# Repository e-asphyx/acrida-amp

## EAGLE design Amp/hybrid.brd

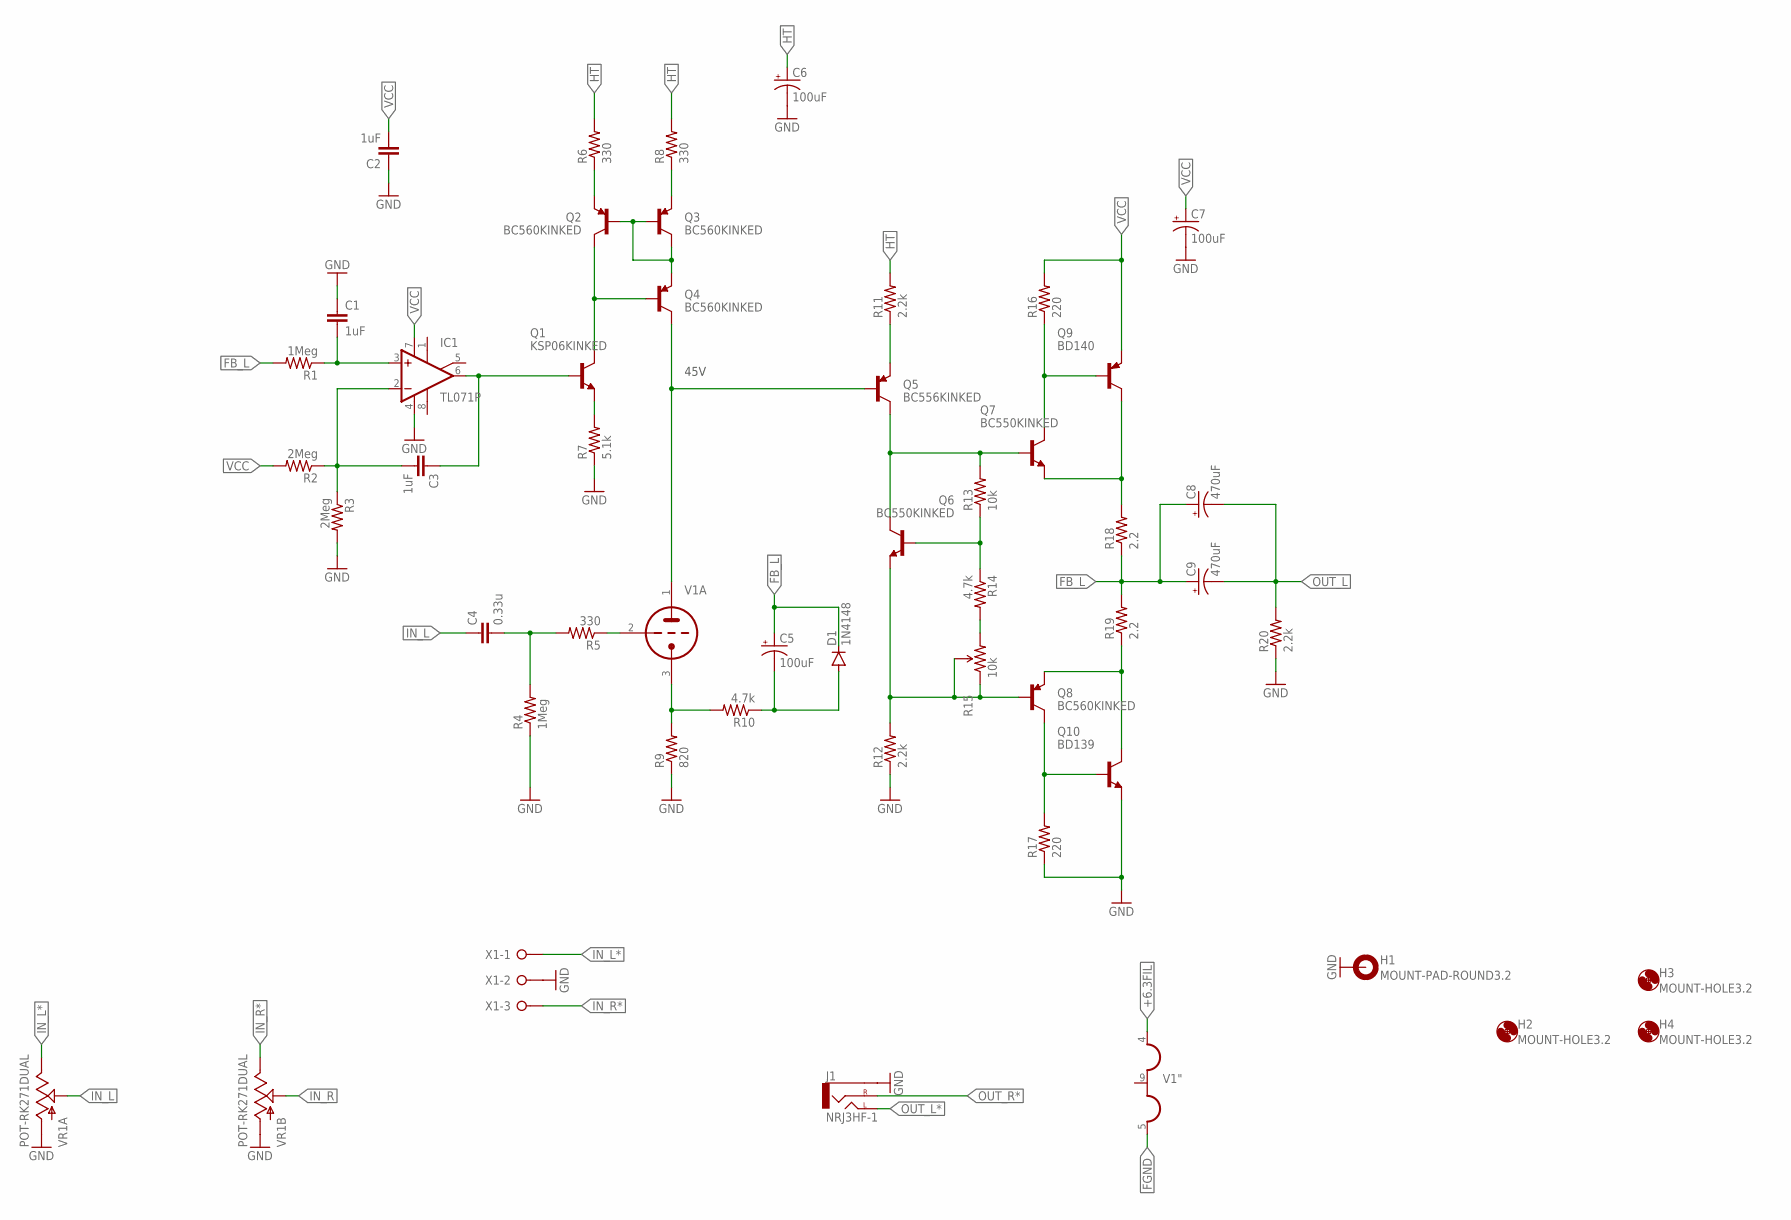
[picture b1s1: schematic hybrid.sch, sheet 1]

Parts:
C1, C3: 1uF; C5B5
C2: 1uF; CAP-PTH-SMALL
C4: 0.33u; C5B7.2
C5: 100uF; CPOL-RADIAL-8/3.5
C6, C7: 100uF; CPOL-RADIAL-12.5/5
C8, C9: 470uF; CPOL-RADIAL-12.5/5
D1: 1N4148; DIODE-1N4148
H1: MOUNT-PAD-ROUND3.2; 3,2-PAD
H2, H3, H4: MOUNT-HOLE3.2; 3,2
IC1: TL071P; DIL08
J1: NRJ3HF-1; NRJ3HF
Q1: KSP06KINKED; TO92-BENT
Q2, Q3, Q4, Q8: BC560KINKED; TO92-BENT
Q5: BC556KINKED; TO92-BENT
Q6, Q7: BC550KINKED; TO92-BENT
Q9: BD140; TO126
Q10: BD139; TO126
R1, R4: 1Meg; AXIAL-0.4
R2, R3: 2Meg; AXIAL-0.4
R5, R6, R8: 330; AXIAL-0.4
R7: 5.1k; AXIAL-0.4
R9: 820; AXIAL-0.4
R10, R14: 4.7k; AXIAL-0.4
R11, R12, R20: 2.2k; AXIAL-0.4
R13: 10k; AXIAL-0.4
R15: 10k; 3362U-2
R16, R17: 220; AXIAL-0.4
R18, R19: 2.2; AXIAL-0.4
V1: 6DJ8-P21MM-BASE; NOVAL-21MM
VR1: POT-RK271DUAL; RK271+PTD902
X1: W237-3E

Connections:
+6.3FIL: V1.4 (H1); also elsewhere on the board
CAT_L: R9.P$2 (2), R10.P$2 (2), V1.3 (TK)
FB_L: C5.1 (+), C8.+, C9.+, D1.C, R1.P$2 (2), R18.P$1 (1), R19.P$2 (2)
FGND: V1.5 (H3); also elsewhere on the board
GND: C1.1, C2.1, C6.-, C7.-, H1.B3,2, IC1.4 (V-), J1.S (SLEEVE), Q10.1 (E), R3.P$2 (2), R4.P$1 (1), R7.P$1 (1), R9.P$1 (1), R12.P$1 (1), R17.P$1 (1), R20.P$1 (1), VR1.1.1.1 (A), VR1.1.1.2 (A), VR1.2.1.1 (A), VR1.2.1.2 (A), X1.2; also elsewhere on the board
G_L: C4.2, R4.P$2 (2), R5.P$2 (2)
HT: C6.+, R6.P$2 (2), R8.P$2 (2), R11.P$2 (2); also elsewhere on the board
IN_L: C4.1, VR1.1.2 (S)
IN_L*: VR1.1.3.1 (E), VR1.1.3.2 (E), X1.1
IN_R: VR1.2.2.1 (S), VR1.2.2.2 (S); also elsewhere on the board
IN_R*: VR1.2.3.1 (E), VR1.2.3.2 (E), X1.3
ISET_L: Q1.3 (C), Q2.1 (C), Q4.2 (B)
unnamed: Q2.2 (B), Q3.1 (C), Q3.2 (B), Q4.3 (E)
unnamed: Q3.3 (E), R8.P$1 (1)
unnamed: Q2.3 (E), R6.P$1 (1)
unnamed: C5.2 (-), D1.A, R10.P$1 (1)
unnamed: Q5.3 (E), R11.P$1 (1)
unnamed: R5.P$1 (1), V1.2 (TG)
unnamed: Q5.1 (C), Q6.1 (C), Q7.2 (B), R13.P$2 (2)
unnamed: Q6.2 (B), R13.P$1 (1), R14.P$1 (1)
unnamed: R14.P$2 (2), R15.3 (CW)
unnamed: Q7.3 (E), Q9.2 (C), R18.P$2 (2)
unnamed: Q6.3 (E), Q8.2 (B), R12.P$2 (2), R15.1 (CCW), R15.2 (WIPER)
unnamed: Q8.3 (E), Q10.2 (C), R19.P$1 (1)
unnamed: Q7.1 (C), Q9.3 (B), R16.P$1 (1)
unnamed: Q8.1 (C), Q10.3 (B), R17.P$2 (2)
unnamed: C3.1, IC1.6 (OUT), Q1.2 (B)
unnamed: C3.2, IC1.2 (-IN), R2.P$1 (1), R3.P$1 (1)
unnamed: C1.2, IC1.3 (+IN), R1.P$1 (1)
unnamed: Q1.1 (E), R7.P$2 (2)
OUT_L: C8.-, C9.-, R20.P$2 (2); also elsewhere on the board
OUT_L*: J1.T (LEFT); also elsewhere on the board
OUT_R*: J1.R (RIGHT); also elsewhere on the board
PL_L: Q4.1 (C), Q5.2 (B), V1.1 (TA)
VCC: C2.2, C7.+, IC1.7 (V+), Q9.1 (E), R2.P$2 (2), R16.P$2 (2); also elsewhere on the board

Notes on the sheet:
45V

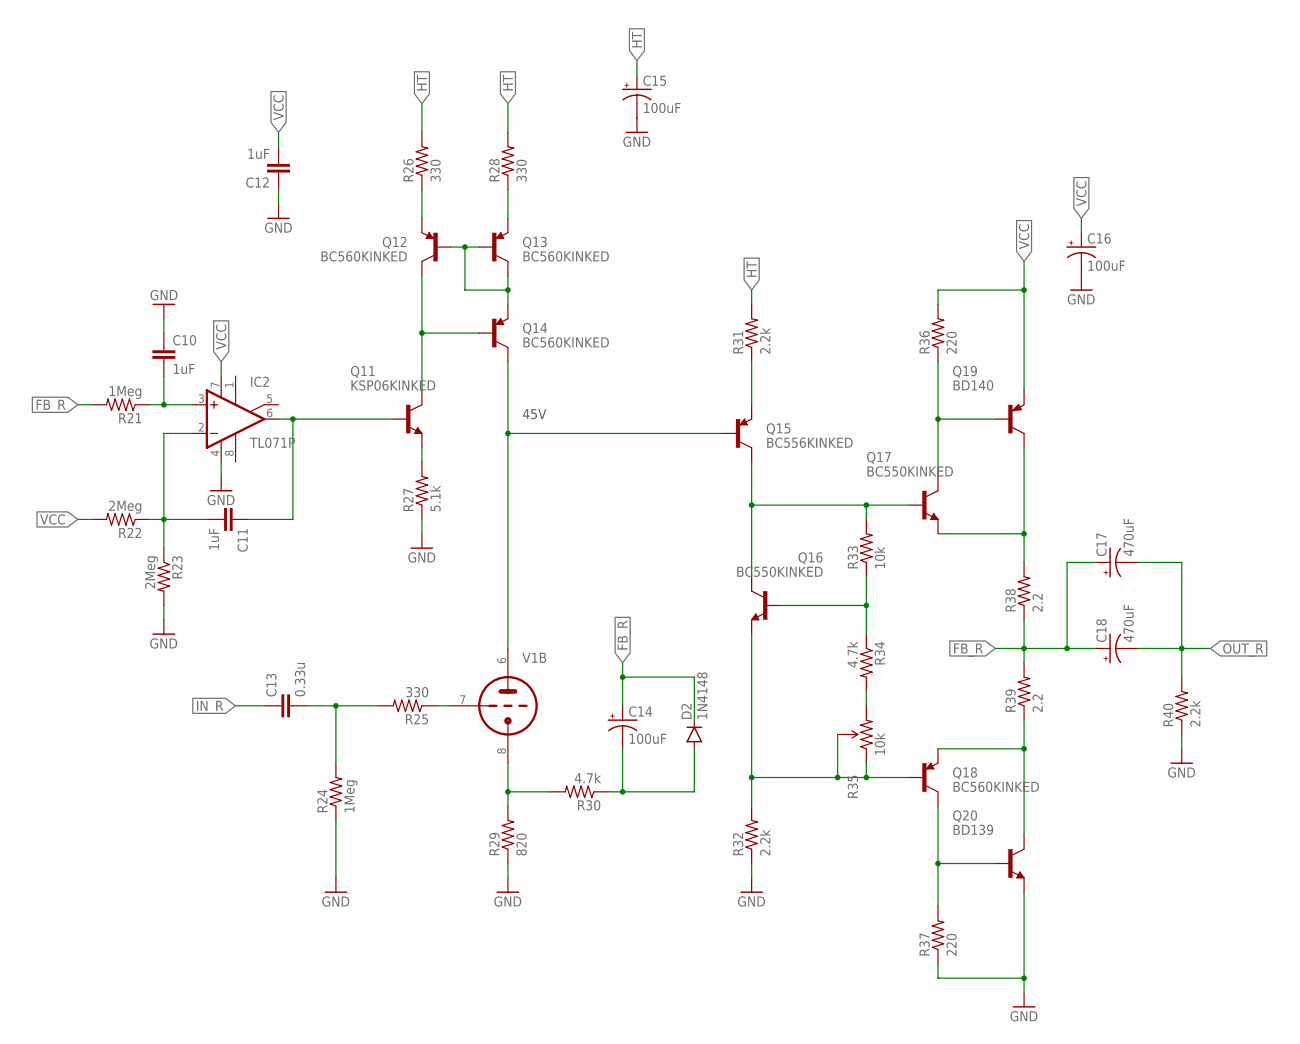
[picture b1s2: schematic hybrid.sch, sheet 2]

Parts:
C10, C11: 1uF; C5B5
C12: 1uF; CAP-PTH-SMALL
C13: 0.33u; C5B7.2
C14: 100uF; CPOL-RADIAL-8/3.5
C15, C16: 100uF; CPOL-RADIAL-12.5/5
C17, C18: 470uF; CPOL-RADIAL-12.5/5
D2: 1N4148; DIODE-1N4148
IC2: TL071P; DIL08
Q11: KSP06KINKED; TO92-BENT
Q12, Q13, Q14, Q18: BC560KINKED; TO92-BENT
Q15: BC556KINKED; TO92-BENT
Q16, Q17: BC550KINKED; TO92-BENT
Q19: BD140; TO126
Q20: BD139; TO126
R21, R24: 1Meg; AXIAL-0.4
R22, R23: 2Meg; AXIAL-0.4
R25, R26, R28: 330; AXIAL-0.4
R27: 5.1k; AXIAL-0.4
R29: 820; AXIAL-0.4
R30, R34: 4.7k; AXIAL-0.4
R31, R32, R40: 2.2k; AXIAL-0.4
R33: 10k; AXIAL-0.4
R35: 10k; 3362U-2
R36, R37: 220; AXIAL-0.4
R38, R39: 2.2; AXIAL-0.4
V1: 6DJ8-P21MM-BASE; NOVAL-21MM

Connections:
CAT_R: R29.P$2 (2), R30.P$2 (2), V1.8 (TK)
FB_R: C14.1 (+), C17.+, C18.+, D2.C, R21.P$2 (2), R38.P$1 (1), R39.P$2 (2)
GND: C10.1, C12.1, C15.-, C16.-, IC2.4 (V-), Q20.1 (E), R23.P$2 (2), R24.P$1 (1), R27.P$1 (1), R29.P$1 (1), R32.P$1 (1), R37.P$1 (1), R40.P$1 (1); also elsewhere on the board
G_R: C13.2, R24.P$2 (2), R25.P$2 (2)
HT: C15.+, R26.P$2 (2), R28.P$2 (2), R31.P$2 (2); also elsewhere on the board
IN_R: C13.1; also elsewhere on the board
ISET_R: Q11.3 (C), Q12.1 (C), Q14.2 (B)
unnamed: R25.P$1 (1), V1.7 (TG)
unnamed: Q13.3 (E), R28.P$1 (1)
unnamed: Q12.2 (B), Q13.1 (C), Q13.2 (B), Q14.3 (E)
unnamed: C14.2 (-), D2.A, R30.P$1 (1)
unnamed: Q15.3 (E), R31.P$1 (1)
unnamed: Q15.1 (C), Q16.1 (C), Q17.2 (B), R33.P$2 (2)
unnamed: Q16.2 (B), R33.P$1 (1), R34.P$1 (1)
unnamed: R34.P$2 (2), R35.3 (CW)
unnamed: Q16.3 (E), Q18.2 (B), R32.P$2 (2), R35.1 (CCW), R35.2 (WIPER)
unnamed: Q17.3 (E), Q19.2 (C), R38.P$2 (2)
unnamed: Q18.3 (E), Q20.2 (C), R39.P$1 (1)
unnamed: Q17.1 (C), Q19.3 (B), R36.P$1 (1)
unnamed: Q18.1 (C), Q20.3 (B), R37.P$2 (2)
unnamed: Q12.3 (E), R26.P$1 (1)
unnamed: C11.2, IC2.2 (-IN), R22.P$1 (1), R23.P$1 (1)
unnamed: C10.2, IC2.3 (+IN), R21.P$1 (1)
unnamed: C11.1, IC2.6 (OUT), Q11.2 (B)
unnamed: Q11.1 (E), R27.P$2 (2)
OUT_R: C17.-, C18.-, R40.P$2 (2); also elsewhere on the board
PL_R: Q14.1 (C), Q15.2 (B), V1.6 (TA)
VCC: C12.2, C16.+, IC2.7 (V+), Q19.1 (E), R22.P$2 (2), R36.P$2 (2); also elsewhere on the board

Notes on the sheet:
45V

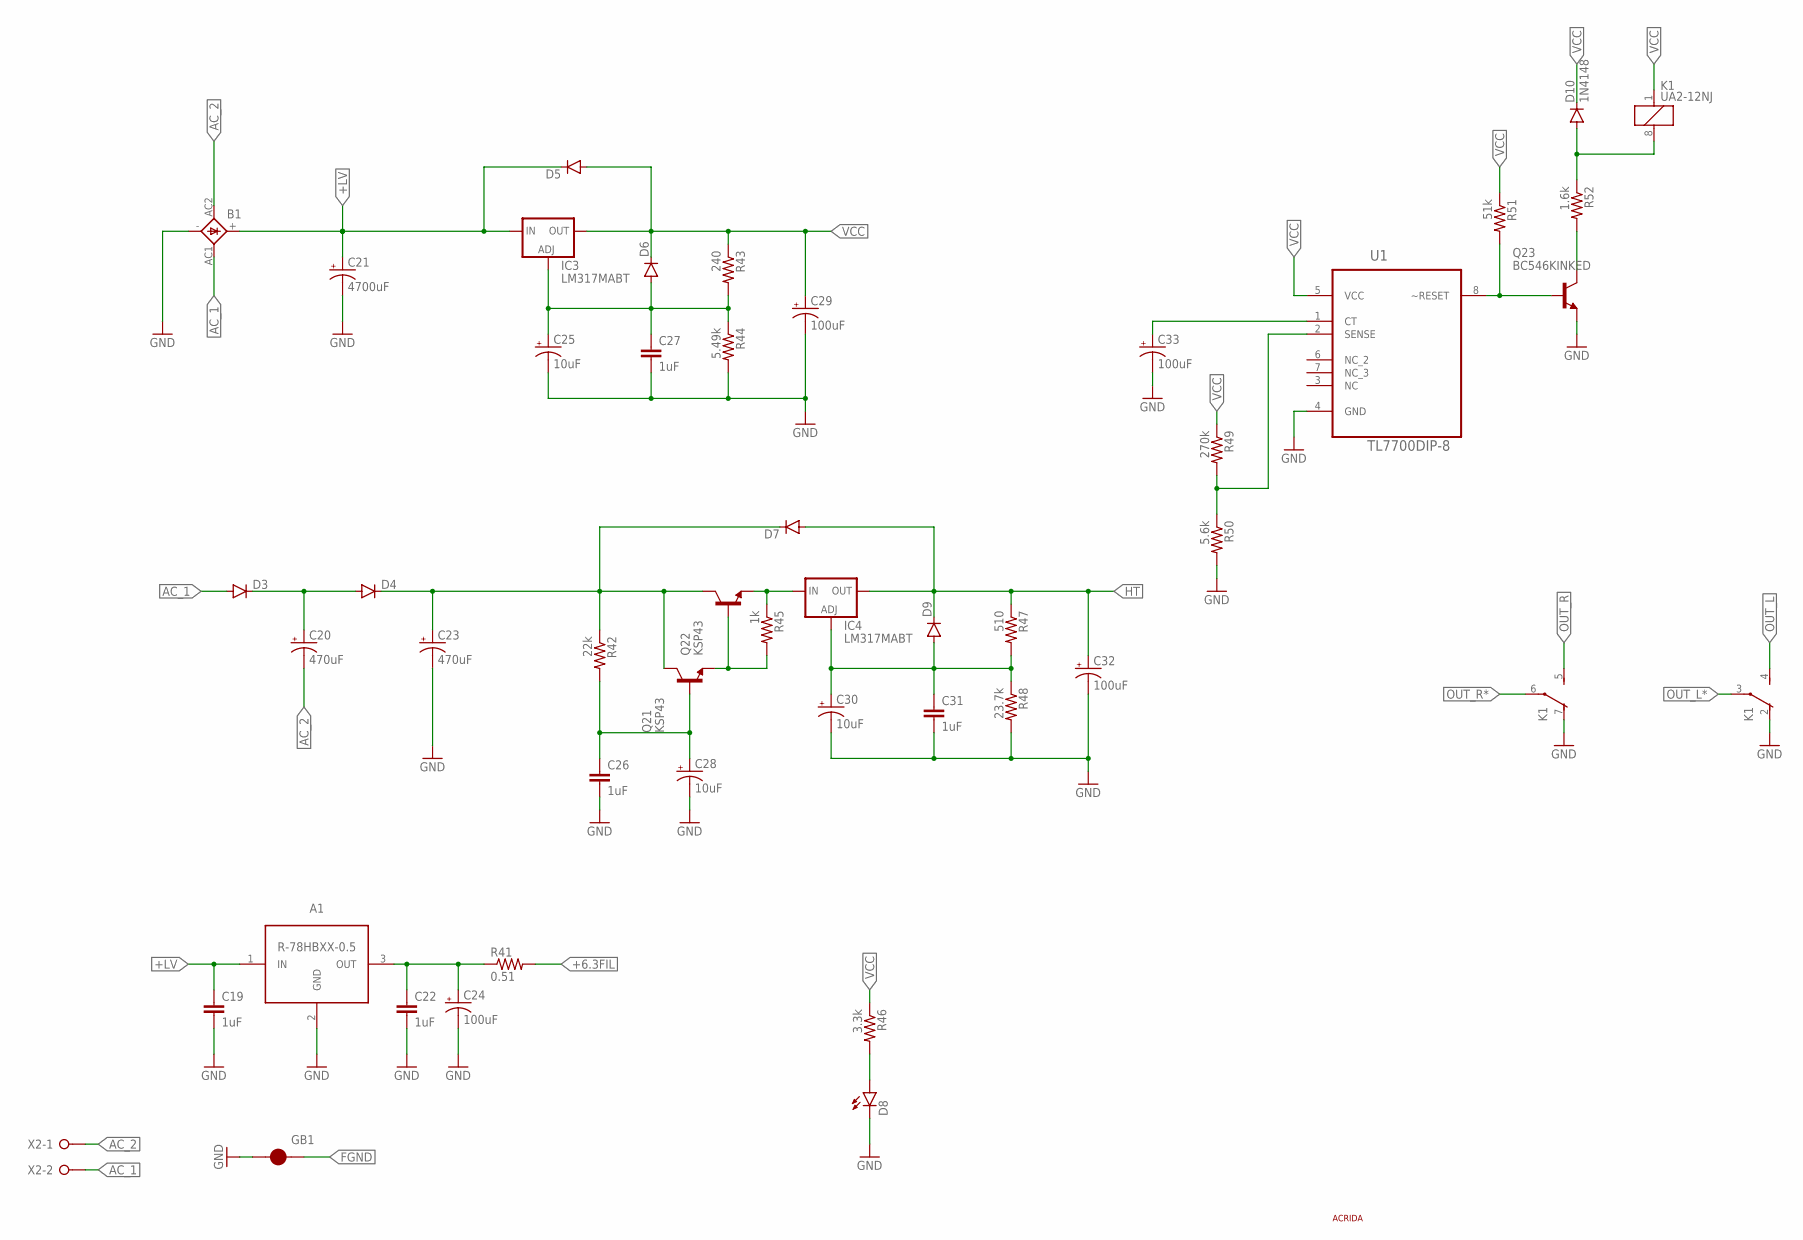
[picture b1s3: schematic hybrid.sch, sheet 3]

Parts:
A1: R-78HBXX-0.5; R-78HB
B1: GBU4; GBU4S
C19, C26: 1uF; CAP-PTH-5MM
C20, C23: 470uF; CPOL-SNAPIN-22/10
C21: 4700uF; CPOL-SNAPIN-30/10
C22, C27, C31: 1uF; CAP-PTH-SMALL
C24, C33: 100uF; CPOL-RADIAL-6.5/2.5
C25, C30: 10uF; CPOL-RADIAL-6.5/2.5
C28: 10uF; CPOL-RADIAL-12/5
C29, C32: 100uF; CPOL-RADIAL-12.5/5
D3, D4, D5, D6, D7, D9: DIODEPTH; DIODE-1N4001
D8: LED3MM
D10: 1N4148; DIODE-1N4148
GB1: COPPER-BRIDGESM; COPPER-BRIDGE-SM
IC3, IC4: LM317MABT; TO220L1
K1: UA2-12NJ; UA2
LOGO1: ACRIDA-LOGO
Q21, Q22: KSP43; TO-92
Q23: BC546KINKED; TO92-BENT
R41: 0.51; AXIAL-0.5
R42: 22k; AXIAL-0.4
R43: 240; AXIAL-0.4
R44: 5.49k; AXIAL-0.4
R45: 1k; AXIAL-0.4
R46: 3.3k; AXIAL-0.4
R47: 510; AXIAL-0.4
R48: 23.7k; AXIAL-0.4
R49: 270k; AXIAL-0.4
R50: 5.6k; AXIAL-0.4
R51: 51k; AXIAL-0.4
R52: 1.6k; AXIAL-0.4
U1: TL7700DIP-8; DIL08
X2: W237-2N

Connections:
+6.3FIL: R41.P$2 (2); also elsewhere on the board
+LV: A1.1 (IN), B1.+, C19.1, C21.1 (+), D5.C, IC3.3 (IN)
AC_1: B1.AC1 (AC2), D3.A, X2.2
AC_2: B1.AC2 (AC1), C20.2 (-), X2.1
FGND: GB1.2; also elsewhere on the board
GND: A1.2 (GND), B1.-, C19.2, C21.2 (-), C22.2, C23.2 (-), C24.2 (-), C25.2 (-), C26.2, C27.2, C28.-, C29.-, C30.2 (-), C31.2, C32.-, C33.2 (-), D8.K (C), GB1.1, K1.2 (O), K1.7 (O), Q23.3 (E), R44.P$2 (2), R48.P$2 (2), R50.P$2 (2), U1.4 (GND); also elsewhere on the board
HT: C32.+, D7.A, D9.C, IC4.2 (OUT), R47.P$1 (1); also elsewhere on the board
unnamed: Q21.1 (E), Q22.2 (B), R45.P$2 (2)
unnamed: C25.1 (+), C27.1, D6.A, IC3.1 (ADJ), R43.P$2 (2), R44.P$1 (1)
unnamed: C20.1 (+), D3.C, D4.A
unnamed: A1.3 (OUT), C22.1, C24.1 (+), R41.P$1 (1)
unnamed: C23.1 (+), D4.C, D7.C, Q21.3 (C), Q22.3 (C), R42.P$1 (1)
unnamed: C26.1, C28.+, Q21.2 (B), R42.P$2 (2)
unnamed: C30.1 (+), C31.1, D9.A, IC4.1 (ADJ), R47.P$2 (2), R48.P$1 (1)
unnamed: IC4.3 (IN), Q22.1 (E), R45.P$1 (1)
unnamed: C33.1 (+), U1.1 (CT)
unnamed: Q23.2 (B), R51.P$2 (2), U1.8 (~RESET)
unnamed: R49.P$2 (2), R50.P$1 (1), U1.2 (SENSE)
unnamed: D8.A, R46.P$2 (2)
unnamed: D10.A, K1.8 (2), R52.P$1 (1)
unnamed: Q23.1 (C), R52.P$2 (2)
OUT_L: K1.4 (S); also elsewhere on the board
OUT_L*: K1.3; also elsewhere on the board
OUT_R: K1.5 (S); also elsewhere on the board
OUT_R*: K1.6; also elsewhere on the board
VCC: C29.+, D5.A, D6.C, D10.C, IC3.2 (OUT), K1.1, R43.P$1 (1), R46.P$1 (1), R49.P$1 (1), R51.P$1 (1), U1.5 (VCC); also elsewhere on the board

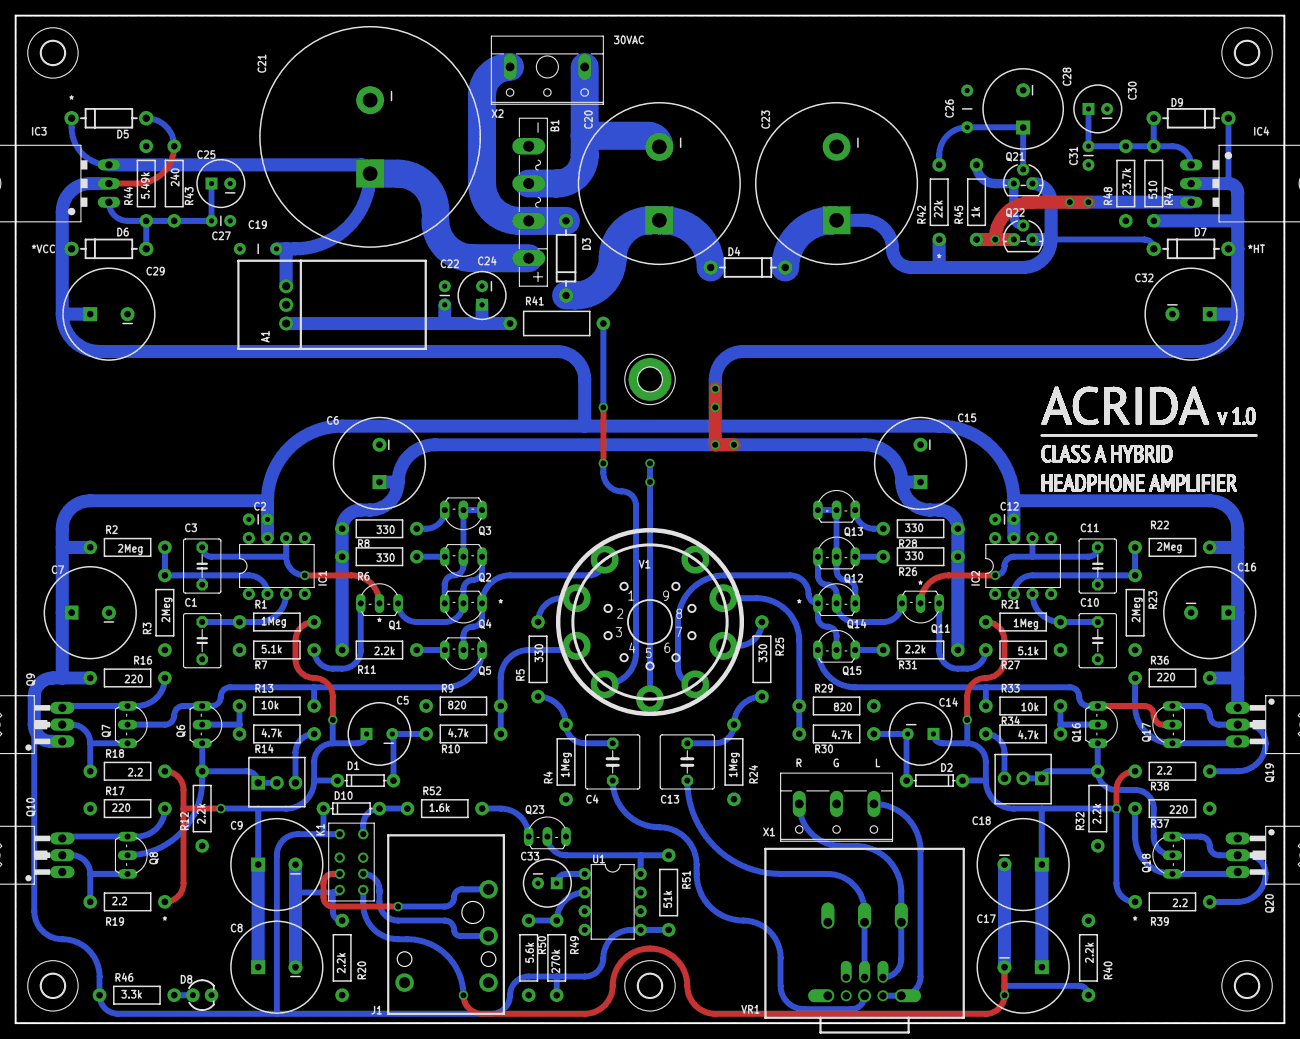
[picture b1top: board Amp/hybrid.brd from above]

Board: 2 copper layers, 172.7 x 137.2 mm, 139 parts (1 on the bottom side), 76 nets.

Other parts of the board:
H5, H6: MOUNT-HOLE3.2; 3,2

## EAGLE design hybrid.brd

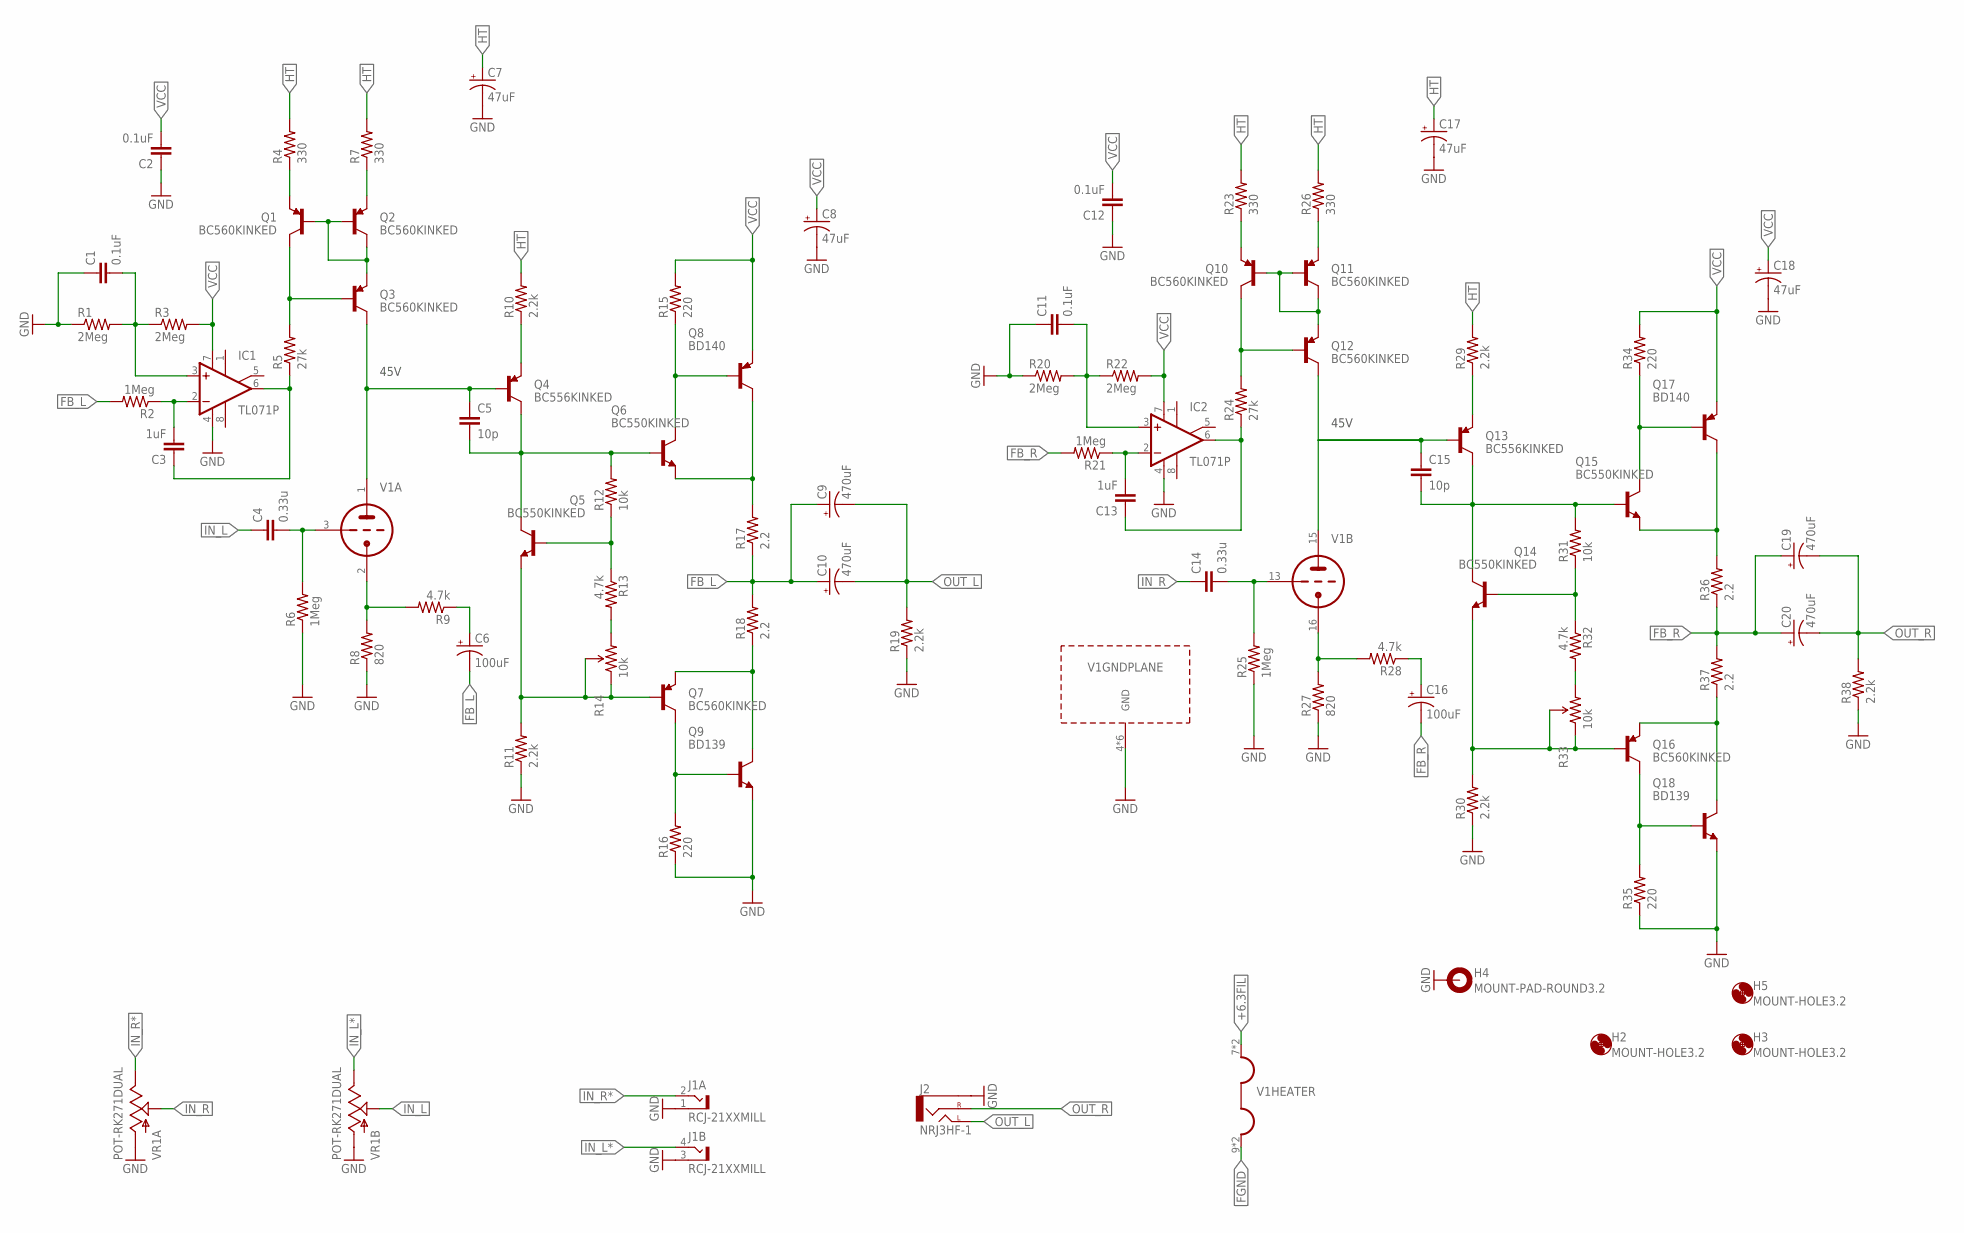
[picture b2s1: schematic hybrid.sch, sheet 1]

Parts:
C1, C2, C11, C12: 0.1uF; CAP-PTH-SMALL
C3, C13: 1uF; C5B5
C4, C14: 0.33u; C5B3.5
C5, C15: 10p; CAP-PTH-SMALL
C6, C16: 100uF; CPOL-RADIAL-8/3.5
C7, C8, C17, C18: 47uF; CPOL-RADIAL-8/3.5
C9, C10, C19, C20: 470uF; CPOL-RADIAL-12.5/5
H2, H3, H5: MOUNT-HOLE3.2; 3,2
H4: MOUNT-PAD-ROUND3.2; 3,2-PAD
IC1, IC2: TL071P; DIL08
J1: RCJ-21XXMILL; RCJ-21-MILL
J2: NRJ3HF-1; NRJ3HF
Q1, Q2, Q3, Q7, Q10, Q11, Q12, Q16: BC560KINKED; TO92-BENT
Q4, Q13: BC556KINKED; TO92-BENT
Q5, Q6, Q14, Q15: BC550KINKED; TO92-BENT
Q8, Q17: BD140; TO126
Q9, Q18: BD139; TO126
R1, R3, R20, R22: 2Meg; AXIAL-0.4
R2, R6, R21, R25: 1Meg; AXIAL-0.4
R4, R7, R23, R26: 330; AXIAL-0.4
R5, R24: 27k; AXIAL-0.4
R8, R27: 820; AXIAL-0.4
R9, R13, R28, R32: 4.7k; AXIAL-0.4
R10, R11, R19, R29, R30, R38: 2.2k; AXIAL-0.4
R12, R31: 10k; AXIAL-0.4
R14, R33: 10k; 3362U-2
R15, R16, R34, R35: 220; AXIAL-0.4
R17, R18, R36, R37: 2.2; AXIAL-0.4
V1: 6DJ8-P-HORIZONTAL; NOVAL-HORIZONTAL
VR1: POT-RK271DUAL; RK271+PTD902

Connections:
+6.3FIL: V1.7 (H1), V1.8 (H1); also elsewhere on the board
CAT_L: R8.P$2 (2), R9.P$2 (2), V1.2 (TK)
CAT_R: R27.P$2 (2), R28.P$2 (2), V1.16 (TK)
FB_L: C6.2 (-), C9.+, C10.+, R2.P$2 (2), R17.P$1 (1), R18.P$2 (2)
FB_R: C16.2 (-), C19.+, C20.+, R21.P$2 (2), R36.P$1 (1), R37.P$2 (2)
FGND: V1.9 (H2), V1.10 (H2); also elsewhere on the board
GND: C1.1, C2.1, C7.2 (-), C8.2 (-), C11.1, C12.1, C17.2 (-), C18.2 (-), H4.B3,2, IC1.4 (V-), IC2.4 (V-), J1.1 (S), J1.3 (S), J2.S (SLEEVE), Q9.1 (E), Q18.1 (E), R1.P$1 (1), R6.P$1 (1), R8.P$1 (1), R11.P$1 (1), R16.P$1 (1), R19.P$1 (1), R20.P$1 (1), R25.P$1 (1), R27.P$1 (1), R30.P$1 (1), R35.P$1 (1), R38.P$1 (1), V1.4 (GND), V1.5 (GND), V1.6 (GND), V1.11 (GND), V1.12 (GND), V1.14 (GND), VR1.1.1.1 (A), VR1.1.1.2 (A), VR1.2.1.1 (A), VR1.2.1.2 (A); also elsewhere on the board
G_L: C4.2, R6.P$2 (2), V1.3 (TG)
G_R: C14.2, R25.P$2 (2), V1.13 (TG)
HT: C7.1 (+), C17.1 (+), R4.P$2 (2), R7.P$2 (2), R10.P$2 (2), R23.P$2 (2), R26.P$2 (2), R29.P$2 (2); also elsewhere on the board
IN_L: C4.1, VR1.2.2.1 (S), VR1.2.2.2 (S)
IN_L*: J1.4 (T), VR1.2.3.1 (E), VR1.2.3.2 (E)
IN_R: C14.1, VR1.1.2 (S)
IN_R*: J1.2 (T), VR1.1.3.1 (E), VR1.1.3.2 (E)
ISET_L: Q1.1 (C), Q3.2 (B), R5.P$2 (2)
ISET_R: Q10.1 (C), Q12.2 (B), R24.P$2 (2)
unnamed: Q1.2 (B), Q2.1 (C), Q2.2 (B), Q3.3 (E)
unnamed: Q2.3 (E), R7.P$1 (1)
unnamed: Q1.3 (E), R4.P$1 (1)
unnamed: C6.1 (+), R9.P$1 (1)
unnamed: Q4.3 (E), R10.P$1 (1)
unnamed: C5.2, Q4.1 (C), Q5.1 (C), Q6.2 (B), R12.P$2 (2)
unnamed: Q5.2 (B), R12.P$1 (1), R13.P$1 (1)
unnamed: R13.P$2 (2), R14.3 (CW)
unnamed: Q6.3 (E), Q8.2 (C), R17.P$2 (2)
unnamed: Q5.3 (E), Q7.2 (B), R11.P$2 (2), R14.1 (CCW), R14.2 (WIPER)
unnamed: Q7.3 (E), Q9.2 (C), R18.P$1 (1)
unnamed: Q6.1 (C), Q8.3 (B), R15.P$1 (1)
unnamed: Q7.1 (C), Q9.3 (B), R16.P$2 (2)
unnamed: Q11.3 (E), R26.P$1 (1)
unnamed: Q10.2 (B), Q11.1 (C), Q11.2 (B), Q12.3 (E)
unnamed: C16.1 (+), R28.P$1 (1)
unnamed: Q13.3 (E), R29.P$1 (1)
unnamed: C15.2, Q13.1 (C), Q14.1 (C), Q15.2 (B), R31.P$2 (2)
unnamed: Q14.2 (B), R31.P$1 (1), R32.P$1 (1)
unnamed: R32.P$2 (2), R33.3 (CW)
unnamed: Q14.3 (E), Q16.2 (B), R30.P$2 (2), R33.1 (CCW), R33.2 (WIPER)
unnamed: Q15.3 (E), Q17.2 (C), R36.P$2 (2)
unnamed: Q16.3 (E), Q18.2 (C), R37.P$1 (1)
unnamed: Q15.1 (C), Q17.3 (B), R34.P$1 (1)
unnamed: Q16.1 (C), Q18.3 (B), R35.P$2 (2)
unnamed: C3.1, IC1.6 (OUT), R5.P$1 (1)
unnamed: C3.2, IC1.2 (-IN), R2.P$1 (1)
unnamed: C1.2, IC1.3 (+IN), R1.P$2 (2), R3.P$1 (1)
unnamed: Q10.3 (E), R23.P$1 (1)
unnamed: C13.1, IC2.6 (OUT), R24.P$1 (1)
unnamed: C13.2, IC2.2 (-IN), R21.P$1 (1)
unnamed: C11.2, IC2.3 (+IN), R20.P$2 (2), R22.P$1 (1)
OUT_L: C9.-, C10.-, J2.T (LEFT), R19.P$2 (2)
OUT_R: C19.-, C20.-, J2.R (RIGHT), R38.P$2 (2)
PL_L: C5.1, Q3.1 (C), Q4.2 (B), V1.1 (TA)
PL_R: C15.1, Q12.1 (C), Q13.2 (B), V1.15 (TA)
VCC: C2.2, C8.1 (+), C12.2, C18.1 (+), IC1.7 (V+), IC2.7 (V+), Q8.1 (E), Q17.1 (E), R3.P$2 (2), R15.P$2 (2), R22.P$2 (2), R34.P$2 (2); also elsewhere on the board

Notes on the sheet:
45V

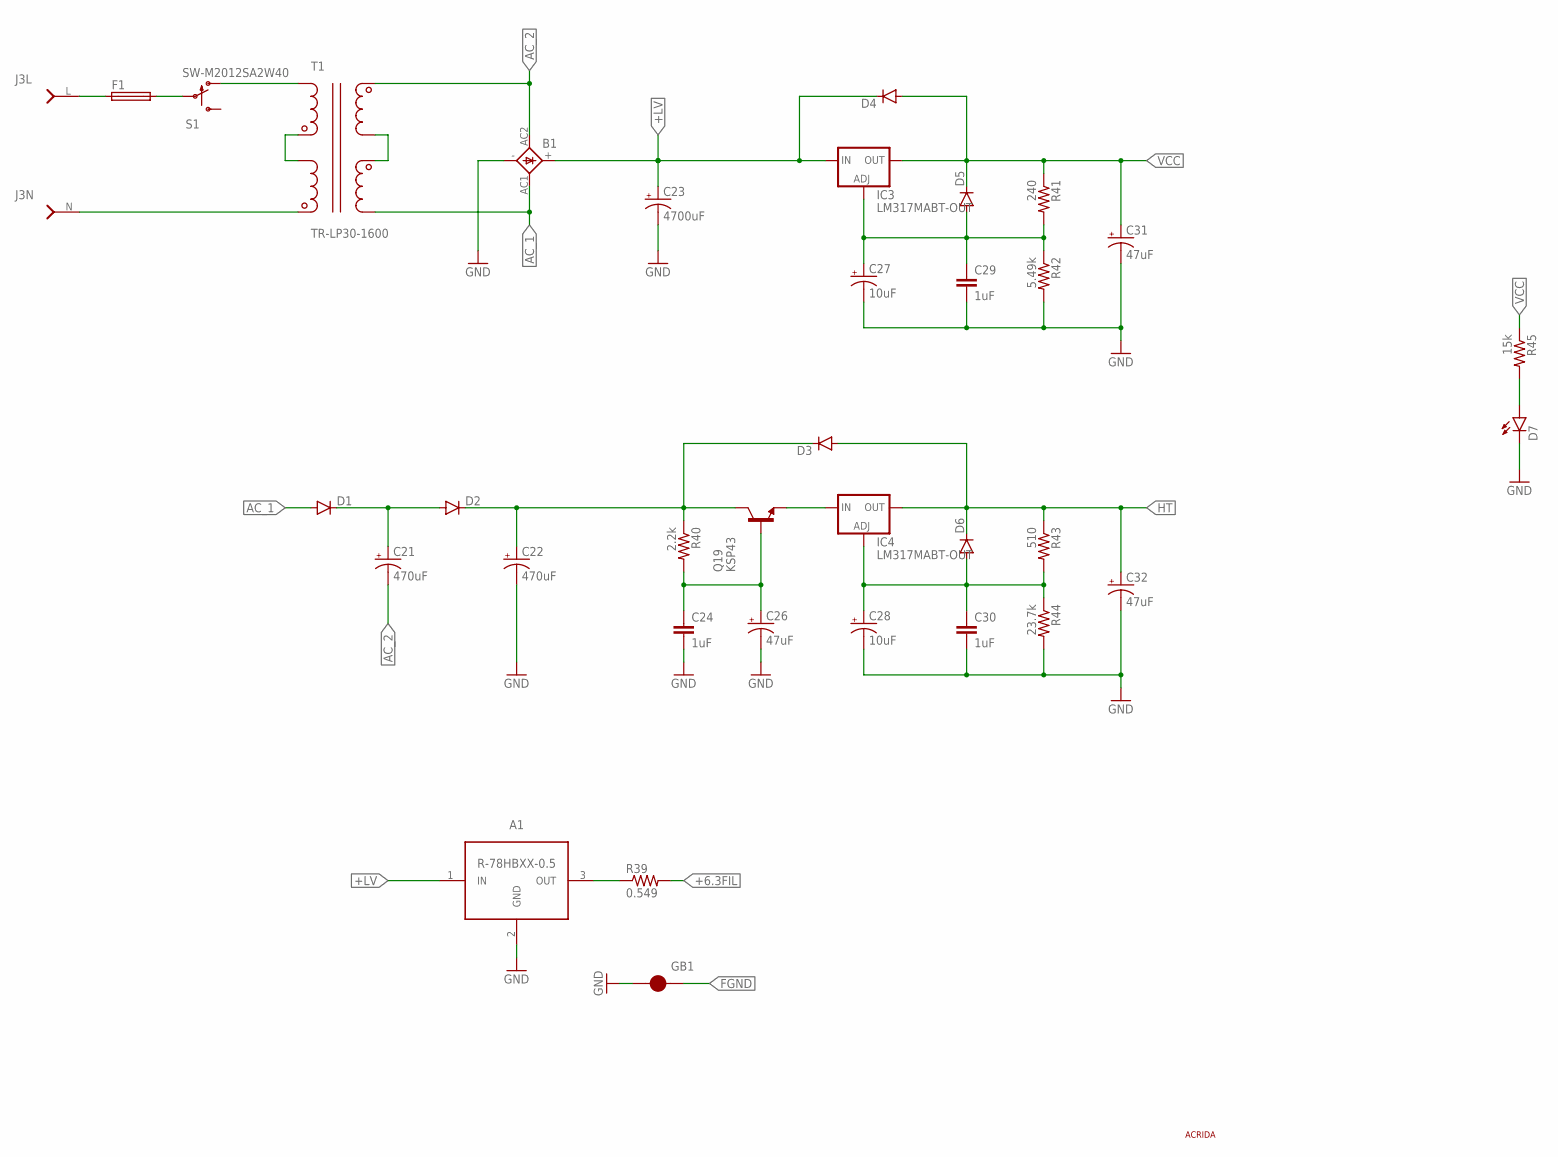
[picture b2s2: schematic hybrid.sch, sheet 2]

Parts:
A1: R-78HBXX-0.5; R-78HB
B1: GBU4; GBU4S
C21, C22: 470uF; CPOL-RADIAL-18/7.5
C23: 4700uF; CPOL-SNAPIN-30/10
C24, C29, C30: 1uF; CAP-PTH-SMALL
C26: 47uF; CPOL-RADIAL-12/5
C27: 10uF; CPOL-RADIAL-5/2.5
C28: 10uF; CPOL-RADIAL-6.5/2.5
C31, C32: 47uF; CPOL-RADIAL-8/3.5
D1, D2, D3, D4, D5, D6: DIODEPTH; DIODE-1N4001
D7: LED3MM
F1: SH22,5
GB1: COPPER-BRIDGESM; COPPER-BRIDGE-SM
IC3, IC4: LM317MABT-OUT; TO220L1-OUT
J3: 703W-00/54
Q19: KSP43; TO-92
R39: 0.549; AXIAL-0.5
R40: 2.2k; AXIAL-0.4
R41: 240; AXIAL-0.4
R42: 5.49k; AXIAL-0.4
R43: 510; AXIAL-0.4
R44: 23.7k; AXIAL-0.4
R45: 15k; AXIAL-0.4
S1: SW-M2012SA2W40; SW-M2012S2A2G40
T1: TR-LP30-1600
U$1: ACRIDA-LOGO

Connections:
+6.3FIL: R39.P$2 (2); also elsewhere on the board
+LV: A1.1 (IN), B1.+, C23.1 (+), D4.C, IC3.3 (IN)
AC_1: B1.AC1 (AC2), D1.A, T1.8
AC_2: B1.AC2 (AC1), C21.2 (-), T1.5
FGND: GB1.2; also elsewhere on the board
GND: A1.2 (GND), B1.-, C22.2 (-), C23.2 (-), C24.2, C26.-, C27.2 (-), C28.2 (-), C29.2, C30.2, C31.2 (-), C32.2 (-), D7.K (C), GB1.1, R42.P$2 (2), R44.P$2 (2); also elsewhere on the board
HT: C32.1 (+), D3.A, D6.C, IC4.2 (OUT), R43.P$1 (1); also elsewhere on the board
unnamed: T1.2, T1.3
unnamed: T1.6, T1.7
unnamed: J3.N, T1.1
unnamed: C27.1 (+), C29.1, D5.A, IC3.1 (ADJ), R41.P$2 (2), R42.P$1 (1)
unnamed: C21.1 (+), D1.C, D2.A
unnamed: A1.3 (OUT), R39.P$1 (1)
unnamed: C22.1 (+), D2.C, D3.C, Q19.3 (C), R40.P$1 (1)
unnamed: C24.1, C26.+, Q19.2 (B), R40.P$2 (2)
unnamed: C28.1 (+), C30.1, D6.A, IC4.1 (ADJ), R43.P$2 (2), R44.P$1 (1)
unnamed: IC4.3 (IN), Q19.1 (E)
unnamed: F1.1, J3.L
unnamed: F1.2, S1.S
unnamed: S1.UP-CONNECT (O), T1.4
unnamed: D7.A, R45.P$2 (2)
P$1: J3.E
VCC: C31.1 (+), D4.A, D5.C, IC3.2 (OUT), R41.P$1 (1), R45.P$1 (1); also elsewhere on the board

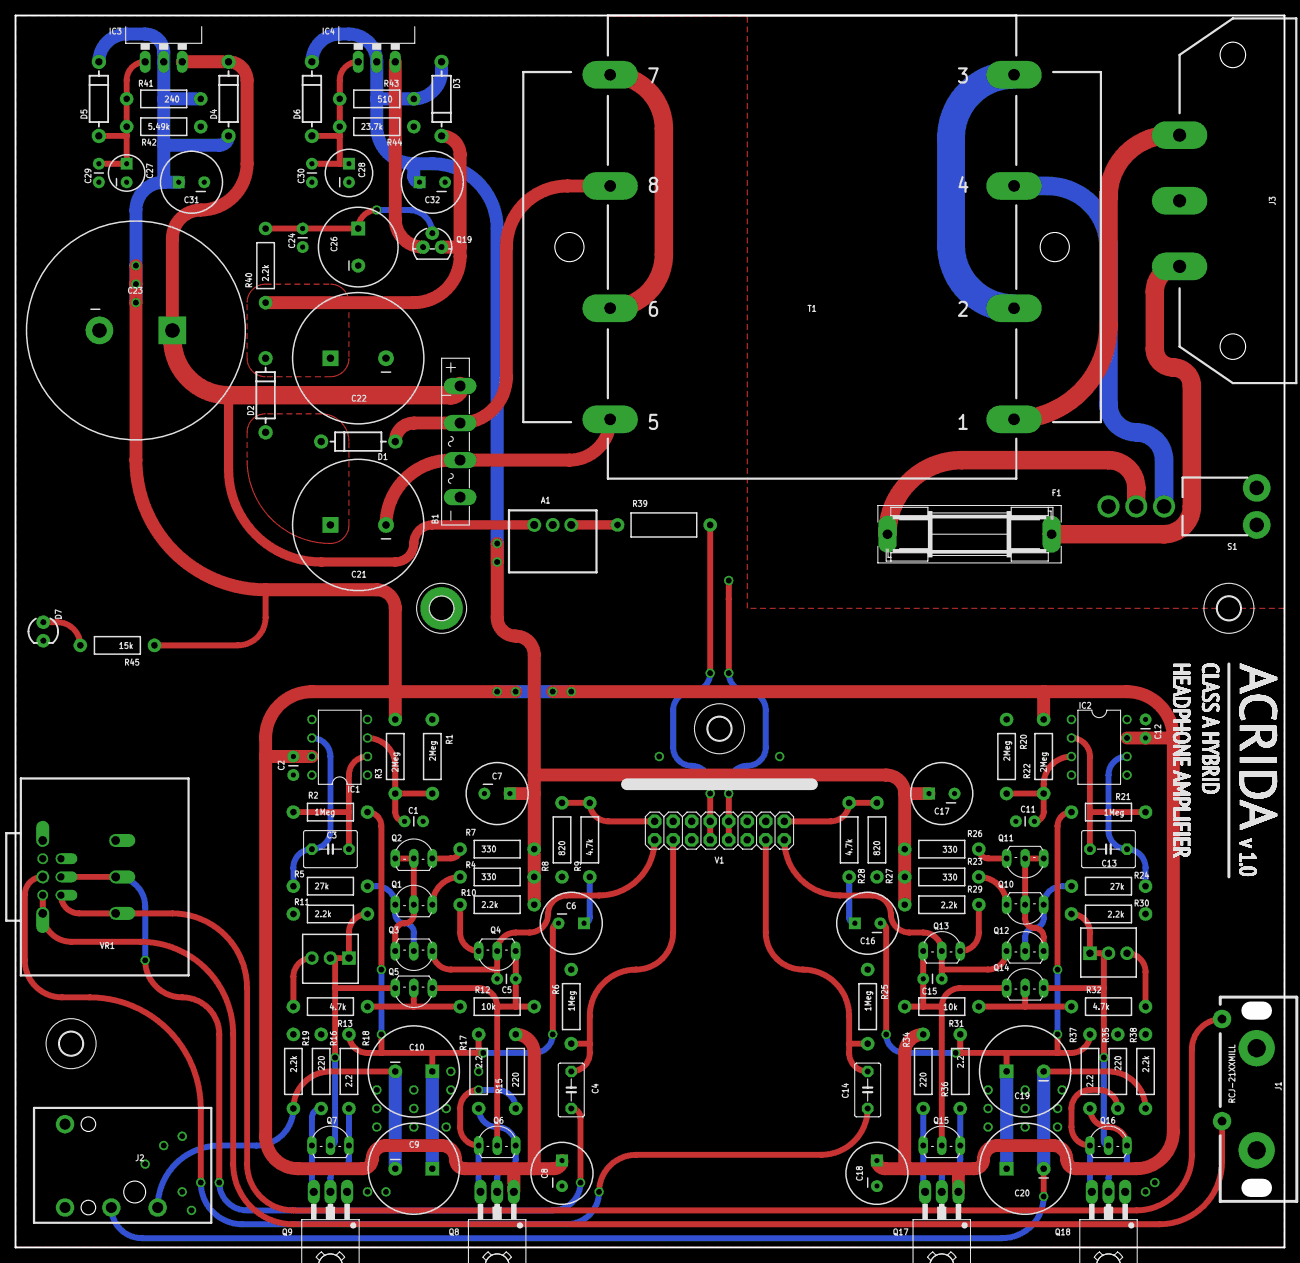
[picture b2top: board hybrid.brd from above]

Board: 2 copper layers, 171.7 x 166.7 mm, 123 parts (1 on the bottom side), 70 nets.

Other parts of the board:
U$2: DANGER-LOGO

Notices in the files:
parts and their libraries:
SparkFun-Capacitors: Licensing: Creative Commons ShareAlike 4.0 International - https://creativecommons.org/licenses/by-sa/4.0
